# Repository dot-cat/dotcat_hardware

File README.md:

# .CAT hardware
Hardware designs for Creative Home Project and not only

## In this repo:
* sr_lights - PCB design of low-power LED driver module with serial interface (based on 8-bit shift register)
* sr_motors - PCB design of low-power motor driver module with serial interface (based on 8-bit shift register)
* sr_motors and sr_lights modules can be easily connected in series; but parrallel connection is recommended for power pins (to not overload input reverse polarity protection transistor)

## Notes:
For reverse polarity protection in cases of high load (more than 3 amps) try to replace an IRLML2244TRPbF transistor with AOD417. Example: https://learn.adafruit.com/16-channel-pwm-servo-driver/downloads

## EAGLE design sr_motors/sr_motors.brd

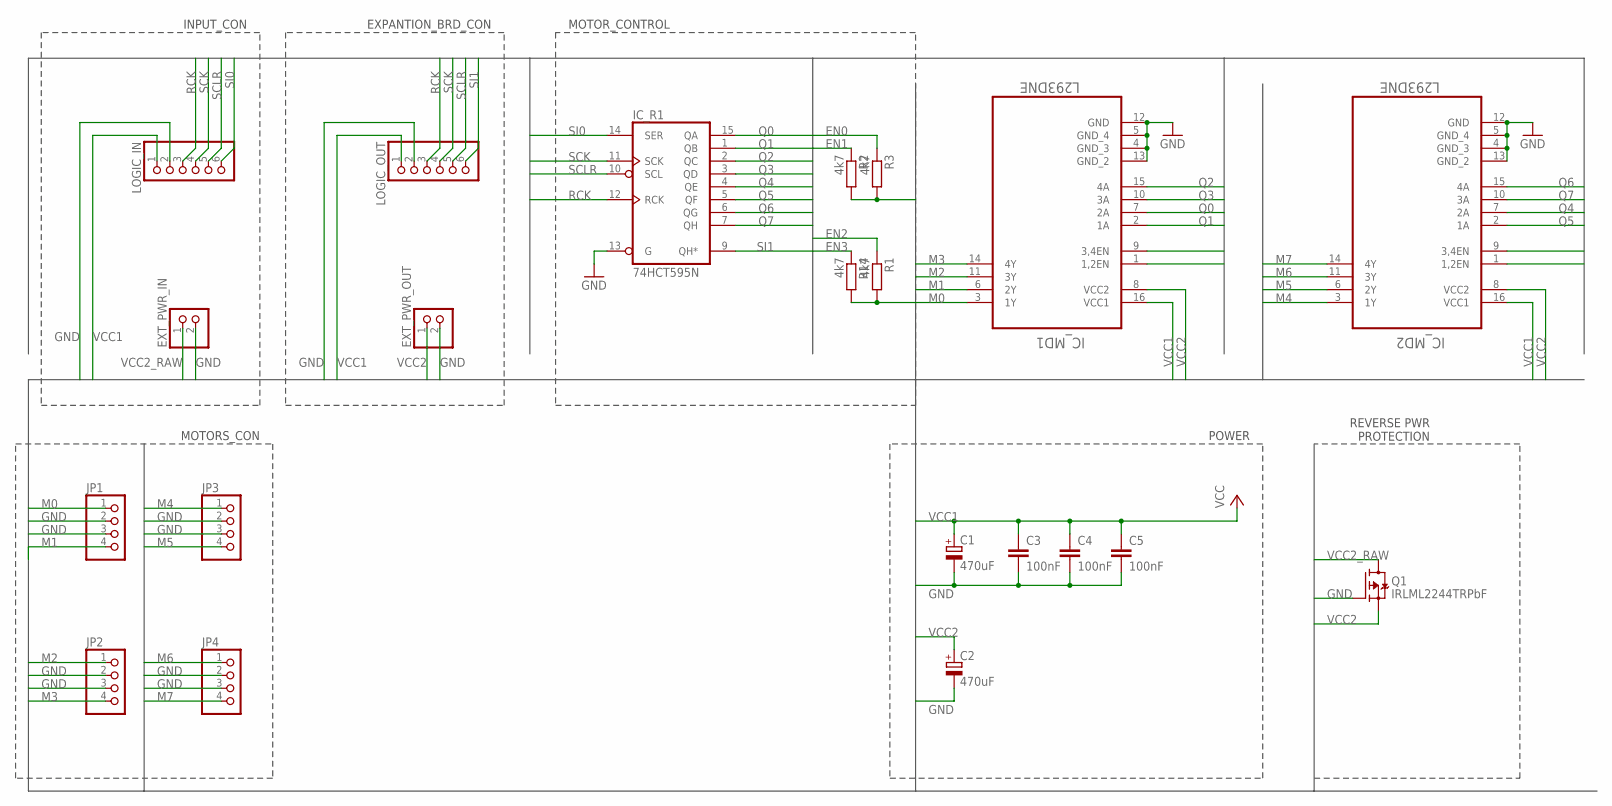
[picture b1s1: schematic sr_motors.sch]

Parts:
C1, C2: 470uF; TT2D6
C3, C4, C5: 100nF; C0805
EXT_PWR_IN: PINHD-1X2; 1X02
EXT_PWR_OUT: PINHD-1X2; 1X02
IC_MD1, IC_MD2: L293DNE; DIP254P762X508-16
IC_R1: 74HCT595N; DIL16
JP1, JP2, JP3, JP4: PINHD-1X4; 1X04
LOGIC_IN: PINHD-1X6; 1X06
LOGIC_OUT: PINHD-1X6; 1X06
Q1: IRLML2244TRPbF; SOT23
R1, R2, R3, R14: 4k7; M0805

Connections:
EN0: IC_MD1.1 (1,2EN), R3.1
EN1: IC_MD1.9 (3,4EN), R2.1
EN2: IC_MD2.1 (1,2EN), R1.1
EN3: IC_MD2.9 (3,4EN), R14.1
GND: C1.-, C2.-, C3.2, C4.2, C5.2, EXT_PWR_IN.2, EXT_PWR_OUT.2, IC_MD1.4 (GND_3), IC_MD1.5 (GND_4), IC_MD1.12 (GND), IC_MD1.13 (GND_2), IC_MD2.4 (GND_3), IC_MD2.5 (GND_4), IC_MD2.12 (GND), IC_MD2.13 (GND_2), IC_R1.8 (GND), IC_R1.13 (G), JP1.2, JP1.3, JP2.2, JP2.3, JP3.2, JP3.3, JP4.2, JP4.3, LOGIC_IN.2, LOGIC_OUT.2, Q1.1 (G)
M0: IC_MD1.3 (1Y), JP1.1
M1: IC_MD1.6 (2Y), JP1.4
M2: IC_MD1.11 (3Y), JP2.1
M3: IC_MD1.14 (4Y), JP2.4
M4: IC_MD2.3 (1Y), JP3.1
M5: IC_MD2.6 (2Y), JP3.4
M6: IC_MD2.11 (3Y), JP4.1
M7: IC_MD2.14 (4Y), JP4.4
Q0: IC_MD1.7 (2A), IC_R1.15 (QA)
Q1: IC_MD1.2 (1A), IC_R1.1 (QB)
Q2: IC_MD1.15 (4A), IC_R1.2 (QC)
Q3: IC_MD1.10 (3A), IC_R1.3 (QD)
Q4: IC_MD2.7 (2A), IC_R1.4 (QE)
Q5: IC_MD2.2 (1A), IC_R1.5 (QF)
Q6: IC_MD2.15 (4A), IC_R1.6 (QG)
Q7: IC_MD2.10 (3A), IC_R1.7 (QH)
RCK: IC_R1.12 (RCK), LOGIC_IN.3, LOGIC_OUT.3
SCK: IC_R1.11 (SCK), LOGIC_IN.4, LOGIC_OUT.4
SCLR: IC_R1.10 (SCL), LOGIC_IN.5, LOGIC_OUT.5
SI0: IC_R1.14 (SER), LOGIC_IN.6
SI1: IC_R1.9 (QH*), LOGIC_OUT.6
VCC1: C1.+, C3.1, C4.1, C5.1, IC_MD1.16 (VCC1), IC_MD2.16 (VCC1), IC_R1.16 (VCC), LOGIC_IN.1, LOGIC_OUT.1, R1.2, R2.2, R3.2, R14.2
VCC2: C2.+, EXT_PWR_OUT.1, IC_MD1.8 (VCC2), IC_MD2.8 (VCC2), Q1.2 (S)
VCC2_RAW: EXT_PWR_IN.1, Q1.3 (D)

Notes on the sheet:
POWER
EXPANTION_BRD_CON
INPUT_CON
MOTOR_CONTROL
MOTORS_CON
REVERSE PWR PROTECTION

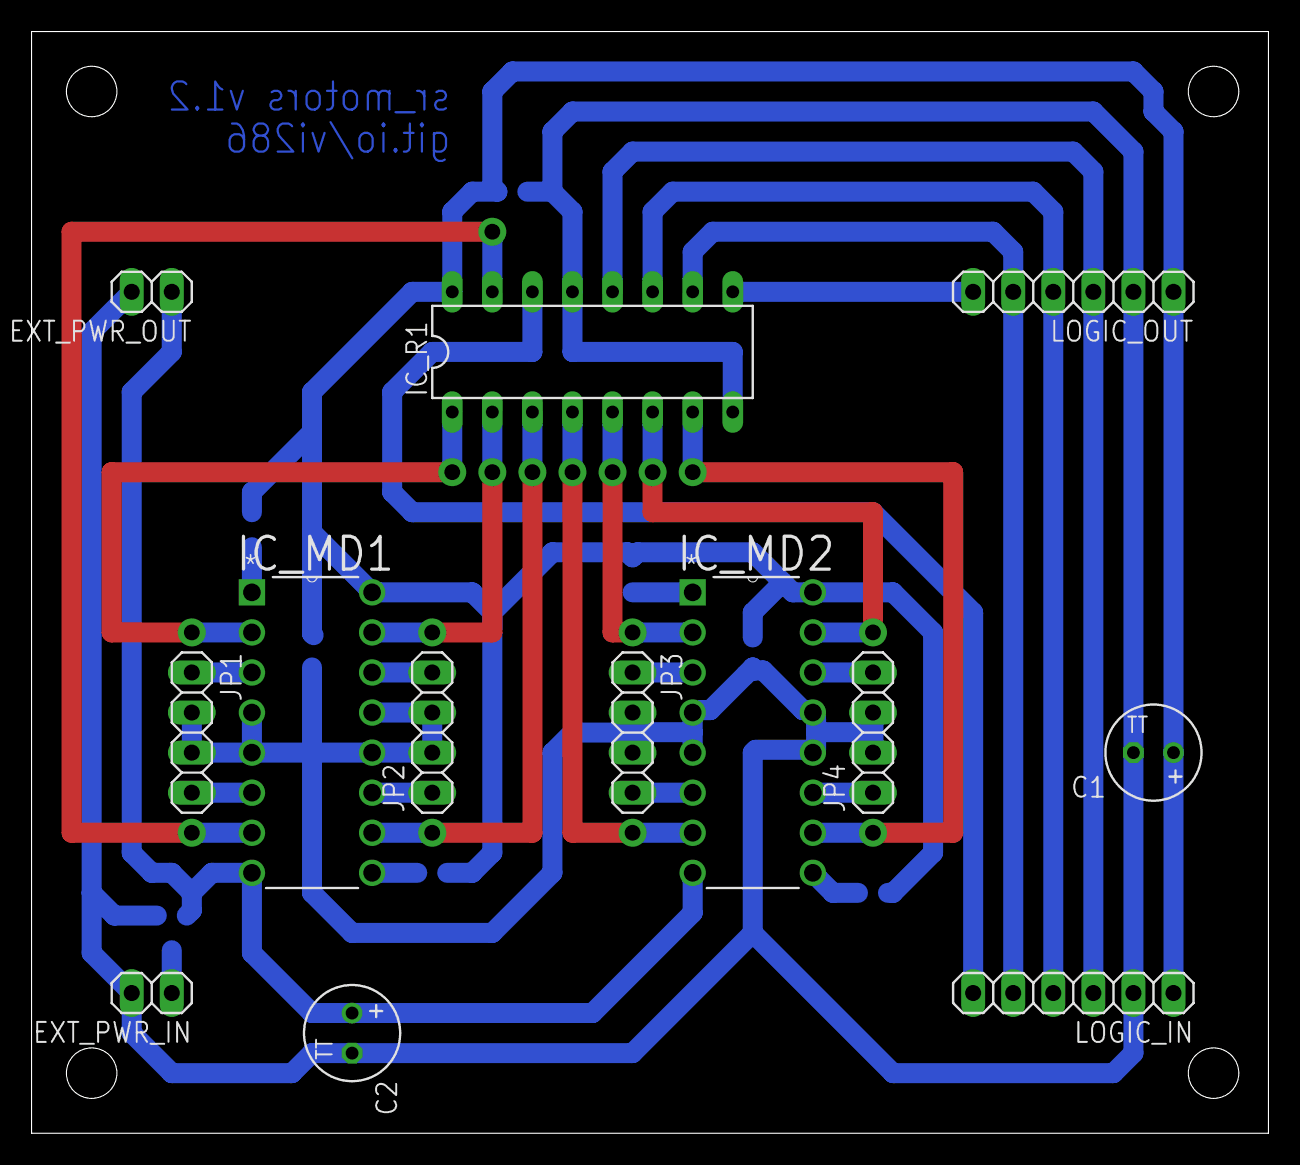
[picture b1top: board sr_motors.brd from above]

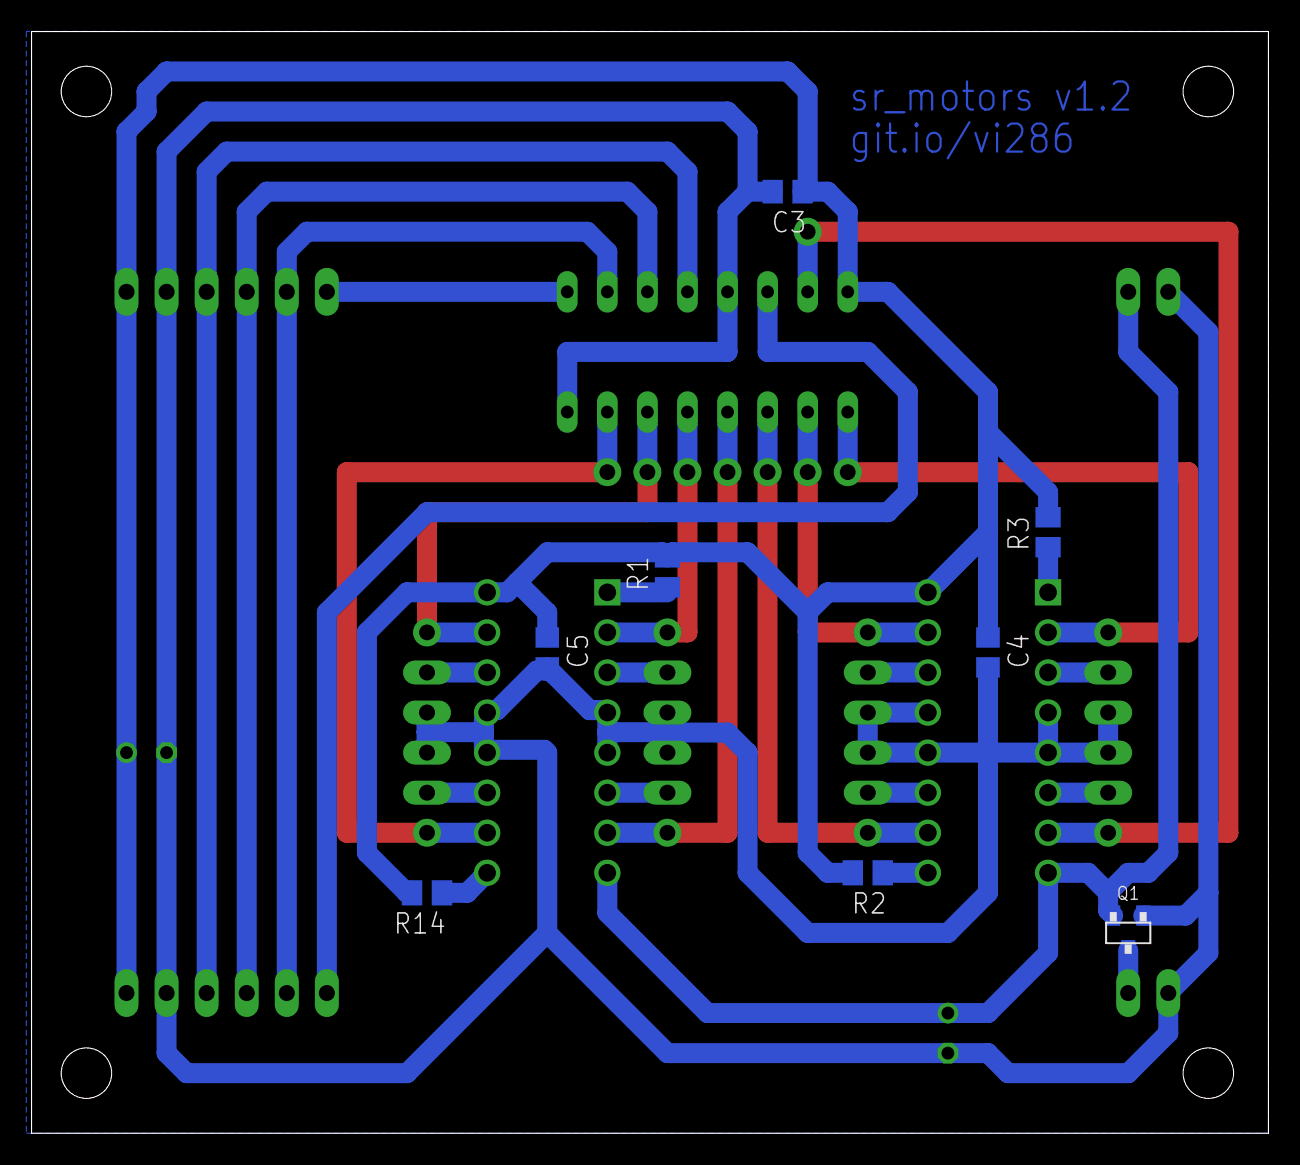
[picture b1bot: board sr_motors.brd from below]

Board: 2 copper layers, 78.4 x 69.8 mm, 21 parts (8 on the bottom side), 29 nets.

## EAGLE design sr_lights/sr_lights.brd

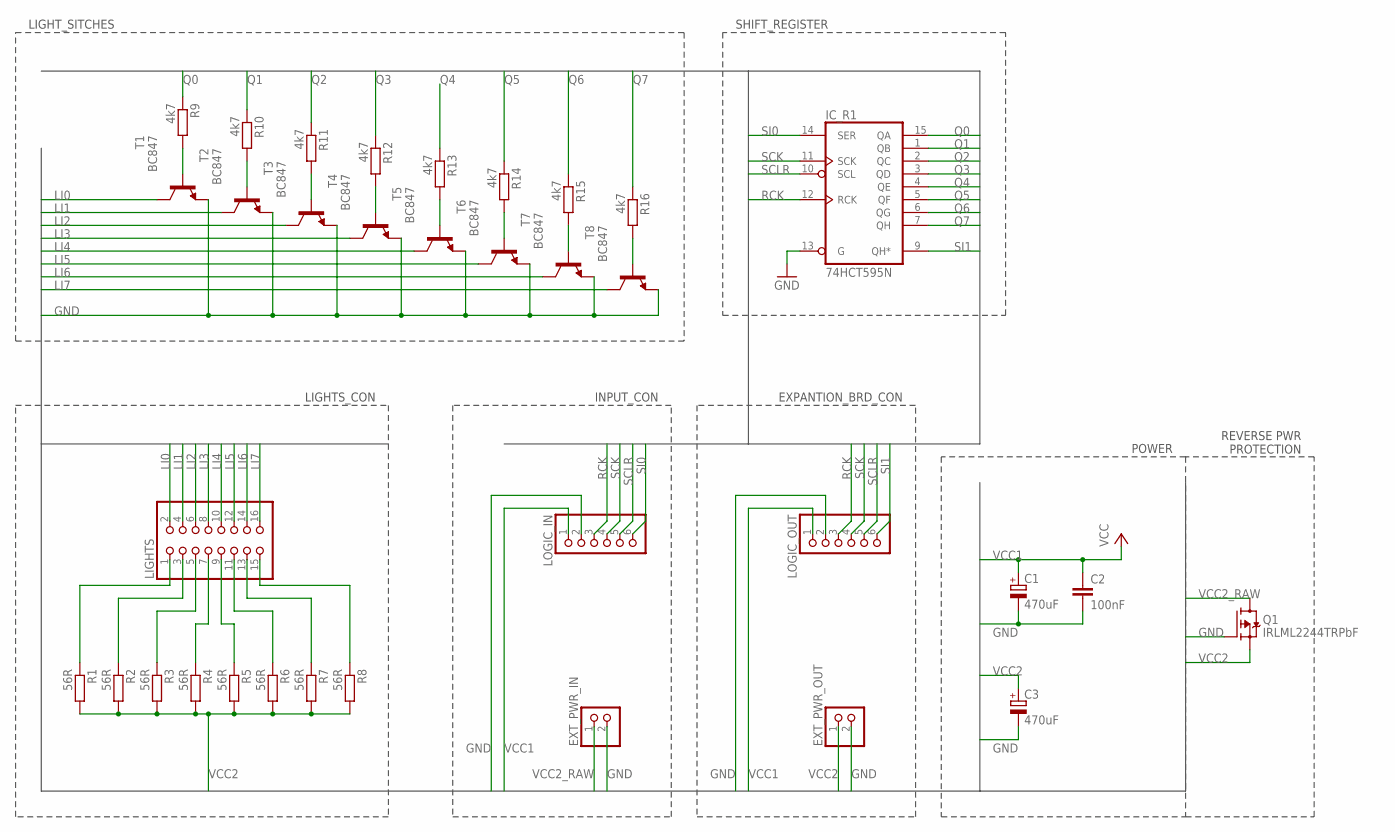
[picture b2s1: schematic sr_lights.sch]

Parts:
C1, C3: 470uF; TT2D6
C2: 100nF; C0805
EXT_PWR_IN: PINHD-1X2; 1X02
EXT_PWR_OUT: PINHD-1X2; 1X02
IC_R1: 74HCT595N; DIL16
LIGHTS: PINHD-2X8; 2X08
LOGIC_IN: PINHD-1X6; 1X06
LOGIC_OUT: PINHD-1X6; 1X06
Q1: IRLML2244TRPbF; SOT23
R1, R2, R3, R4, R5, R6, R7, R8: 56R; M0805
R9, R10, R11, R12, R13, R14, R15, R16: 4k7; M0805
T1, T2, T3, T4, T5, T6, T7, T8: BC847; SOT23

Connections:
GND: C1.-, C2.2, C3.-, EXT_PWR_IN.2, EXT_PWR_OUT.2, IC_R1.8 (GND), IC_R1.13 (G), LOGIC_IN.2, LOGIC_OUT.2, Q1.1 (G), T1.2 (E), T2.2 (E), T3.2 (E), T4.2 (E), T5.2 (E), T6.2 (E), T7.2 (E), T8.2 (E)
LI0: LIGHTS.2, T1.3 (C)
LI1: LIGHTS.4, T2.3 (C)
LI2: LIGHTS.6, T3.3 (C)
LI3: LIGHTS.8, T4.3 (C)
LI4: LIGHTS.10, T5.3 (C)
LI5: LIGHTS.12, T6.3 (C)
LI6: LIGHTS.14, T7.3 (C)
LI7: LIGHTS.16, T8.3 (C)
unnamed: LIGHTS.1, R1.1
unnamed: LIGHTS.3, R2.1
unnamed: LIGHTS.5, R3.1
unnamed: LIGHTS.15, R8.1
unnamed: LIGHTS.13, R7.1
unnamed: R9.2, T1.1 (B)
unnamed: R10.2, T2.1 (B)
unnamed: R11.2, T3.1 (B)
unnamed: R12.2, T4.1 (B)
unnamed: R13.2, T5.1 (B)
unnamed: R14.2, T6.1 (B)
unnamed: LIGHTS.11, R6.1
unnamed: LIGHTS.7, R4.1
unnamed: LIGHTS.9, R5.1
unnamed: R15.2, T7.1 (B)
unnamed: R16.2, T8.1 (B)
Q0: IC_R1.15 (QA), R9.1
Q1: IC_R1.1 (QB), R10.1
Q2: IC_R1.2 (QC), R11.1
Q3: IC_R1.3 (QD), R12.1
Q4: IC_R1.4 (QE), R13.1
Q5: IC_R1.5 (QF), R14.1
Q6: IC_R1.6 (QG), R15.1
Q7: IC_R1.7 (QH), R16.1
RCK: IC_R1.12 (RCK), LOGIC_IN.3, LOGIC_OUT.3
SCK: IC_R1.11 (SCK), LOGIC_IN.4, LOGIC_OUT.4
SCLR: IC_R1.10 (SCL), LOGIC_IN.5, LOGIC_OUT.5
SI0: IC_R1.14 (SER), LOGIC_IN.6
SI1: IC_R1.9 (QH*), LOGIC_OUT.6
VCC1: C1.+, C2.1, IC_R1.16 (VCC), LOGIC_IN.1, LOGIC_OUT.1
VCC2: C3.+, EXT_PWR_OUT.1, Q1.2 (S), R1.2, R2.2, R3.2, R4.2, R5.2, R6.2, R7.2, R8.2
VCC2_RAW: EXT_PWR_IN.1, Q1.3 (D)

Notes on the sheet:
POWER
EXPANTION_BRD_CON
INPUT_CON
SHIFT_REGISTER
LIGHT_SITCHES
LIGHTS_CON
REVERSE PWR PROTECTION

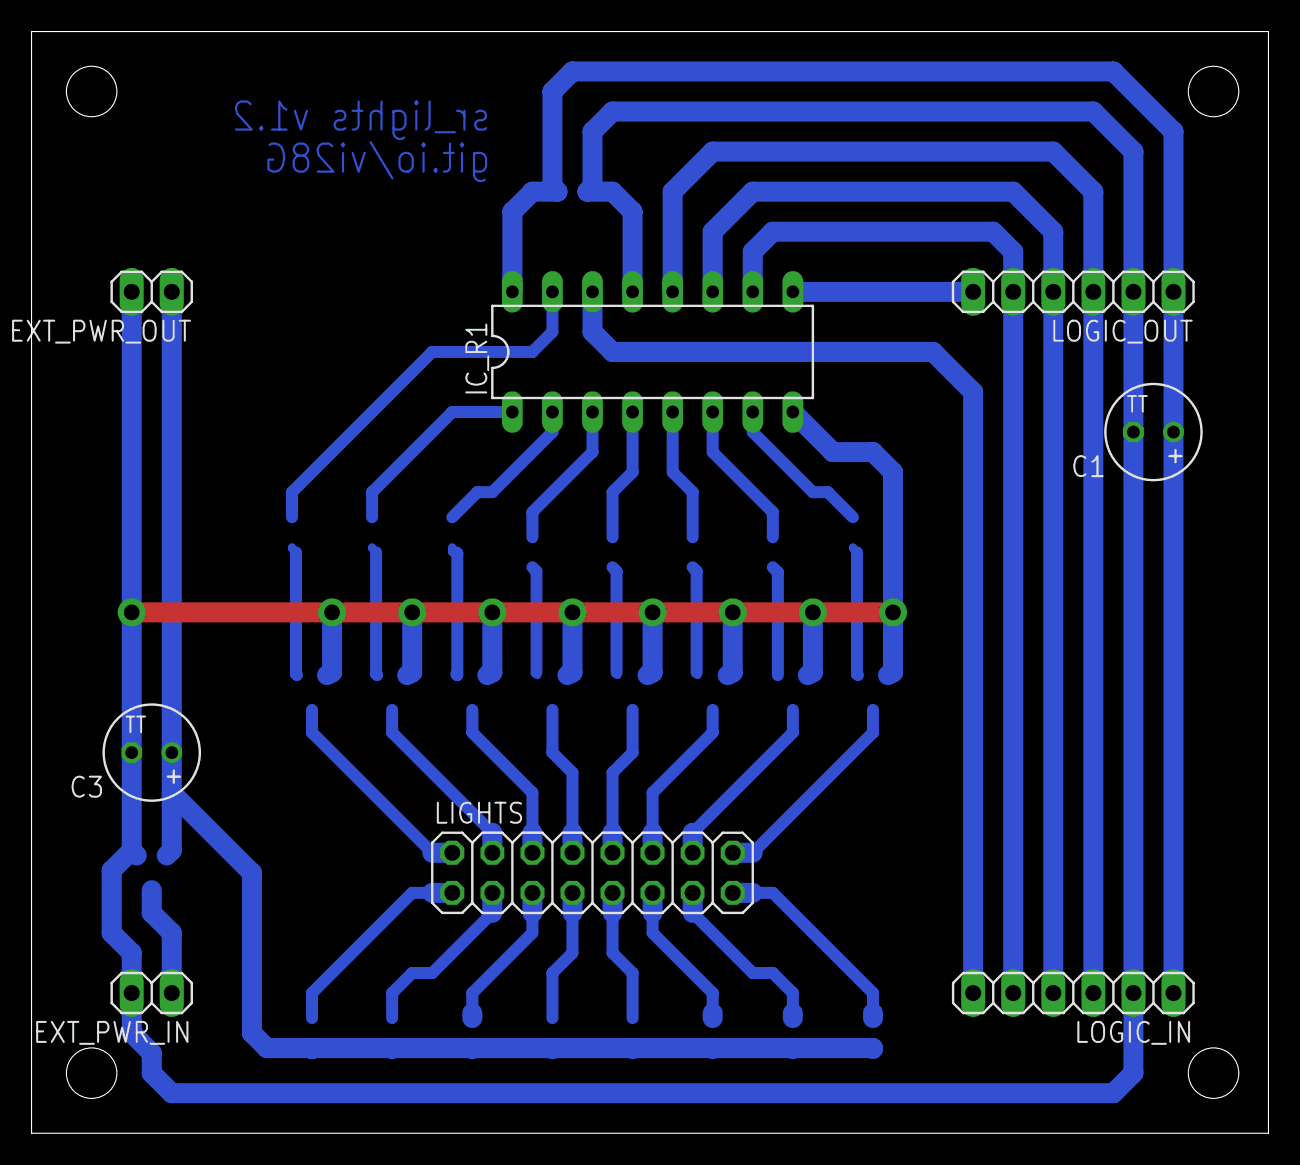
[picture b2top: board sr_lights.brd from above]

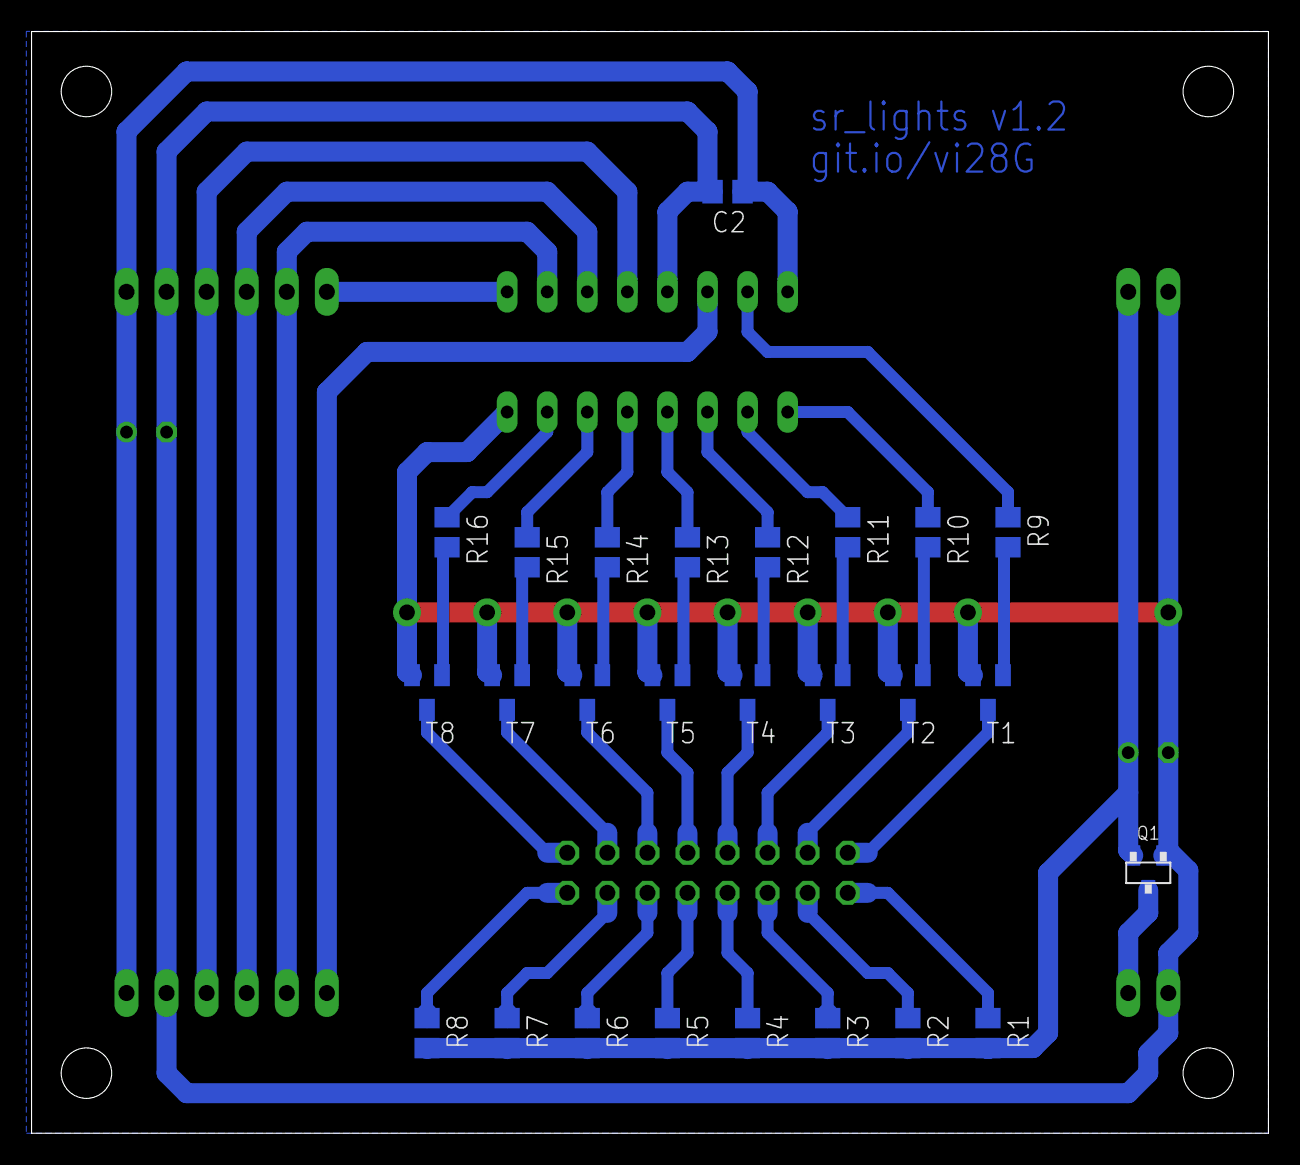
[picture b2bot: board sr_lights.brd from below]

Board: 2 copper layers, 78.4 x 69.8 mm, 34 parts (26 on the bottom side), 41 nets.

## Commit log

2016-08-13 Added sr_lights and sr_motors modules - versions on 03.08.16
2016-08-13 Minor changes in sr_lights: DRC check, GND plane, moved some routes and components
2016-08-13 DRC: Fixes and approves
2016-08-13 Routes and positions - aligned PWR connectors, top right hole - moved C3 capacitor - updated routes - approved some DRC errors (short route segments near pads)
2016-08-13 Added GND plane
2016-08-13 Updated illustration
2016-08-13 Route rework: - increased distance between wires - shifted capacitors, connectors and IC's - rerouted EN signals - other small changes
2016-08-14 Removed license file
    Files in this repository are open source. But it's not an open-source software. It's hardware and hardware designs. So MIT license doesn't fit here
2016-08-15 Fixed Dimension layer
2016-08-15 Added design rules file
2016-08-15 DRC and align: Set the same DRC for lights and motors, fixed new DRC errors in sr_lights, aligned headers
2016-08-22 Added reverse current protection for external power, added version text
2016-09-07 Increased width of power lines on sr_motors
2016-09-13 Icreased width of routes, icreased board width
2016-09-13 Verion 1.2: Increased route width and board width, small other changes
    Squashed commit of the following:
    commit cb5b4ae53fc73325e271569d8207a4f4cb0d995e
    Author: Sergey Kostyuk <contact@s-kostyuk.me>
    Date: Tue Sep 13 19:34:33 2016 +0300
    Increaded width of routes, increased board width, replaced capacitor package, updated board version
    commit 30ef558f6f82cadcaf764826f9decc7df1a17ce0
2016-09-13 Fixed route width in 'low_power' net class
2016-10-28 Transistor notice
2017-02-02 Updated README, restored LICENSE
